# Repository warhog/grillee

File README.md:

# Grillee

## Legal
LotusGrill&reg; is a registered trademark of [LotusGrill GmbH](https://lotusgrill.de).

This project has in no way a connection to the LotusGrill GmbH. It is a private hobby project.

## License
GPLv3 licensed, see [LICENSE.md](license.md).

## Advice
Everything in this repo is provided as it is. I give no guarantee or take any responsibility for it. If you are not experienced with electronics you should at least have someone looking on your final build.

## Details
This project is a digital, bluetooth enabled control unit for LotusGrill&reg; styled grills. These kind of grills normally comes with a simple potentiometer for regulating the fan speed (correlating with the heat produces by the coal). After a few years of heavy usage of my LotusGrill&reg; the potentiometer was broken. Instead of replacing it I decided to create this control unit for improved handling.

Highlights:
* Bluetooth control (using an app)
* Manual (bluetoothless) control
* Fan rpm monitoring
* 2 built in grill thermometer probe connectors for various NTCs
* Battery voltage monitoring
* Alarming buzzer
* Webupdate

## App
The app is currently only available for Android on the Google Play Store. Due to the usage of the [Ionic Framework](https://ionicframework.com/) it can be also compiled for iOS.

Google Play Store: TODO: LINK

## Usage
### Fan control
The fan speed can either be controlled by the potentiometer (manual mode) or the app (using bluetooth). As soon as the app is connected the potentiometer is ignored.

### LED
The RGB LED shows the different states of operation. Blue light shows that the unit is in manual mode (potentiometer controls fan). Green light shows that bluetooth is connected. Both (blue and green light) show the selected fan speed using the brightness. The LED is blinking red in case of errors.

### Alarming

### Probes

### Update
Press the webupdate button and the reset button in parallel. Keep the webupdate button pressed while releasing the reset button and hold for 5 seconds. The board should start up in webupdate mode now. Search for a wifi network called `grillee-....`. The dots are the serial number of the ESP32 module. Connect to the wifi and browse the url: `http://192.168.4.1`. The web ui gives you the option to upload a new software.

## Control unit software
The control unit software is using Arduino on ESP32. The measurement data for the different sensors was taken from the WLANThermo Nano project ([source](https://github.com/WLANThermo-nano/WLANThermo_ESP32_Software/blob/master/src/temperature/TemperatureBase.cpp)).

The board has test pins for the serial connection to initially flash the software.

## Libraries used
MedianFilterLib2 v1.0.0

Mcp3208 v1.4.0

## Hardware
The hardware schematics, gerber files, ... can be found in the `hardware` folder. The components were chosen to be easy to obtain. 
The basic measurement circuit was taken from the WLANThermo Nano project ([schematics](https://github.com/WLANThermo-nano/WLANThermo_nano_Hardware/blob/master/nano%20v1%2B/circuit/Schaltplan%20WLANThermo%20Nano%20V1%2B.pdf)).

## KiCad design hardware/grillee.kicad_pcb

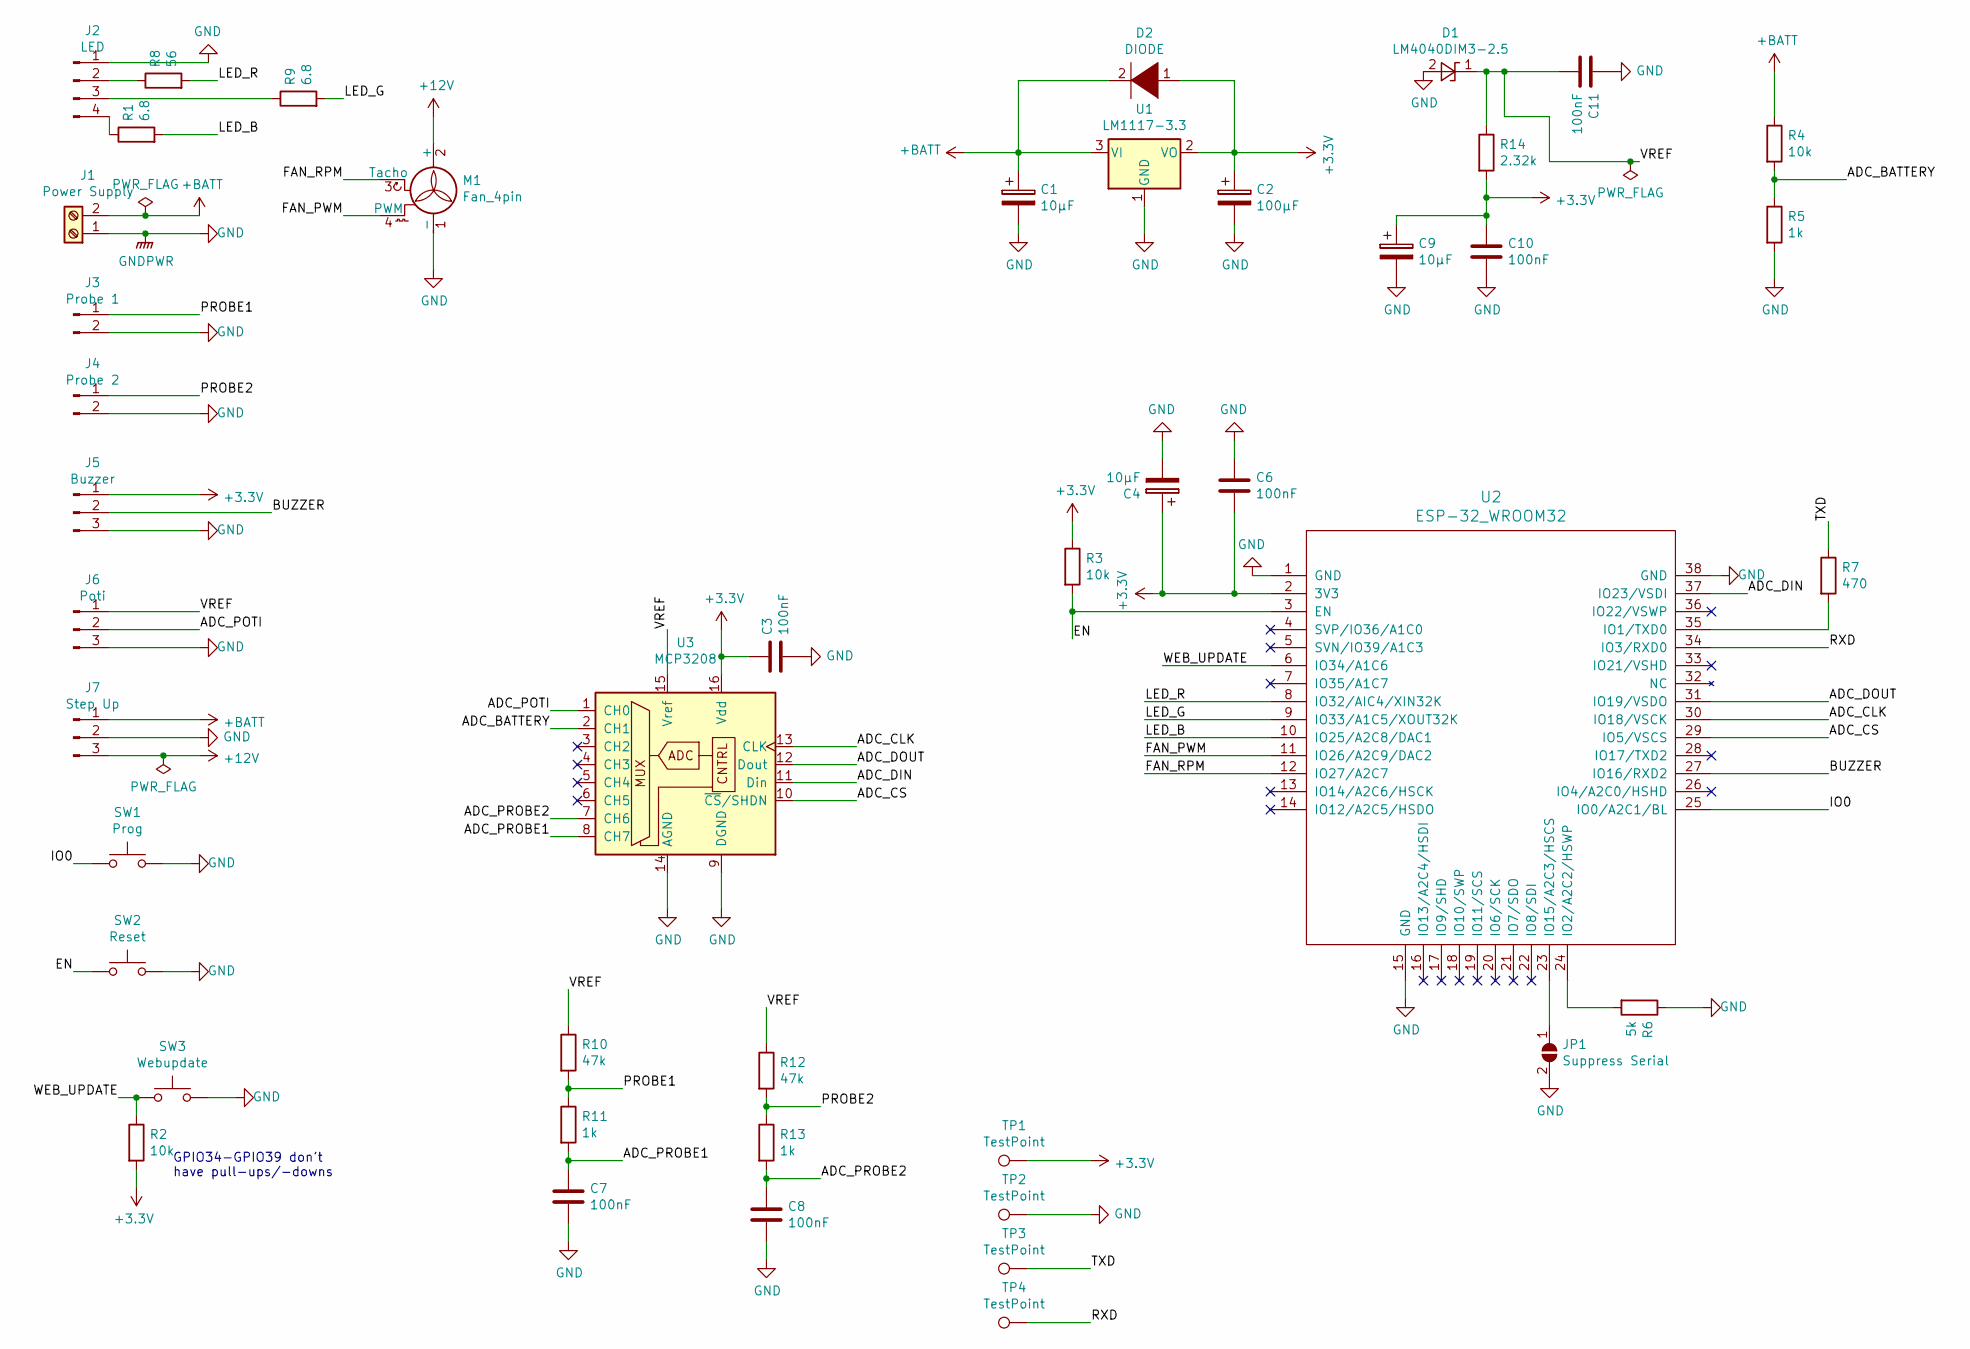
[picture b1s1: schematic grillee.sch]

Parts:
C1, C4: 10µF; CP_Elec_5x4.4
C2: 100µF; CP_Elec_6.3x5.4
C3, C6, C7, C8, C10, C11: 100nF; C_1206_3216Metric_Pad1.42x1.75mm_HandSolder
C9: 10µF; CP_Elec_6.3x5.4
D1: LM4040DIM3-2.5; SOT-23
D2: DIODE; D_SOD-323_HandSoldering
J1: Power Supply; TerminalBlock_RND_205-00287_1x02_P5.08mm_Horizontal
J2: LED; PinHeader_1x04_P2.54mm_Horizontal
J3: Probe 1; PinHeader_1x02_P2.54mm_Horizontal
J4: Probe 2; PinHeader_1x02_P2.54mm_Horizontal
J5: Buzzer; PinHeader_1x03_P2.54mm_Horizontal
J6: Poti; PinHeader_1x03_P2.54mm_Horizontal
J7: Step Up; PinHeader_1x03_P2.54mm_Horizontal
JP1: Suppress Serial; SolderJumper-2_P1.3mm_Open_RoundedPad1.0x1.5mm
M1: Fan_4pin; Molex_KK-254_AE-6410-04A_1x04_P2.54mm_Vertical
R1, R9: 6.8; R_1206_3216Metric_Pad1.42x1.75mm_HandSolder
R2, R3, R4: 10k; R_1206_3216Metric_Pad1.42x1.75mm_HandSolder
R5, R11, R13: 1k; R_1206_3216Metric_Pad1.42x1.75mm_HandSolder
R6: 5k; R_1206_3216Metric_Pad1.42x1.75mm_HandSolder
R7: 470; R_1206_3216Metric_Pad1.42x1.75mm_HandSolder
R8: 56; R_1206_3216Metric_Pad1.42x1.75mm_HandSolder
R10, R12: 47k; R_1206_3216Metric_Pad1.42x1.75mm_HandSolder
R14: 2.32k; R_Axial_DIN0204_L3.6mm_D1.6mm_P7.62mm_Horizontal
SW1: Prog; SW_SPST_KMR2
SW2: Reset; SW_SPST_KMR2
SW3: Webupdate; SW_SPST_KMR2
TP1, TP2, TP3, TP4: TestPoint; TestPoint_Pad_D1.5mm
U1: LM1117-3.3; SOT-223
U2: ESP-32_WROOM32; ESP32-WROOM
U3: MCP3208; SOIC-16_3.9x9.9mm_P1.27mm

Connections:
+3V3: C2.1, C3.1, C4.1, C6.2, C9.1, C10.1, D2.1 (K), J5.1, R2.2, R3.1, R14.2, TP1.1, U1.2 (VO), U2.2 (3V3), U3.16 (Vdd)
+12V: J7.3, M1.2 (+)
+BATT: C1.1, D2.2 (A), J1.2, J7.1, R4.1, U1.3 (VI)
/ADC_BATTERY: R4.2, R5.1, U3.2 (CH1)
/ADC_CLK: U2.30 (IO18/VSCK), U3.13 (CLK)
/ADC_CS: U2.29 (IO5/VSCS), U3.10 (~CS~/SHDN)
/ADC_DIN: U2.37 (IO23/VSDI), U3.11 (Din)
/ADC_DOUT: U2.31 (IO19/VSDO), U3.12 (Dout)
/ADC_POTI: J6.2, U3.1 (CH0)
/ADC_PROBE1: C7.1, R11.2, U3.8 (CH7)
/ADC_PROBE2: C8.1, R13.2, U3.7 (CH6)
/BUZZER: J5.2, U2.27 (IO16/RXD2)
/EN: R3.2, SW2.1, U2.3 (EN)
/FAN_PWM: M1.4 (PWM), U2.11 (IO26/A2C9/DAC2)
/FAN_RPM: M1.3 (Tacho), U2.12 (IO27/A2C7)
/IO0: SW1.1, U2.25 (IO0/A2C1/BL)
/LED_B: R1.2, U2.10 (IO25/A2C8/DAC1)
/LED_G: R9.2, U2.9 (IO33/A1C5/XOUT32K)
/LED_R: R8.2, U2.8 (IO32/AIC4/XIN32K)
/PROBE1: J3.1, R10.2, R11.1
/PROBE2: J4.1, R12.2, R13.1
/RXD: TP4.1, U2.34 (IO3/RXD0)
/TXD: R7.1, TP3.1
/VREF: C11.2, D1.1 (K), J6.1, R10.1, R12.1, R14.1, U3.15 (Vref)
/WEB_UPDATE: R2.1, SW3.1, U2.6 (IO34/A1C6)
GND: C1.2, C2.2, C3.2, C4.2, C6.1, C7.2, C8.2, C9.2, C10.2, C11.1, D1.2 (A), J1.1, J2.1, J3.2, J4.2, J5.3, J6.3, J7.2, JP1.2 (B), M1.1 (-), R5.2, R6.1, SW1.2, SW2.2, SW3.2, TP2.1, U1.1 (GND), U2.1 (GND), U2.15 (GND), U2.38 (GND), U3.9 (DGND), U3.14 (AGND)
unnamed: J2.2, R8.1
unnamed: J2.3, R9.1
unnamed: J2.4, R1.1
unnamed: JP1.1 (A), U2.23 (IO15/A2C3/HSCS)
unnamed: R6.2, U2.24 (IO2/A2C2/HSWP)
unnamed: R7.2, U2.35 (IO1/TXD0)

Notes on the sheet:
GPIO34-GPIO39 don't have pull-ups/-downs

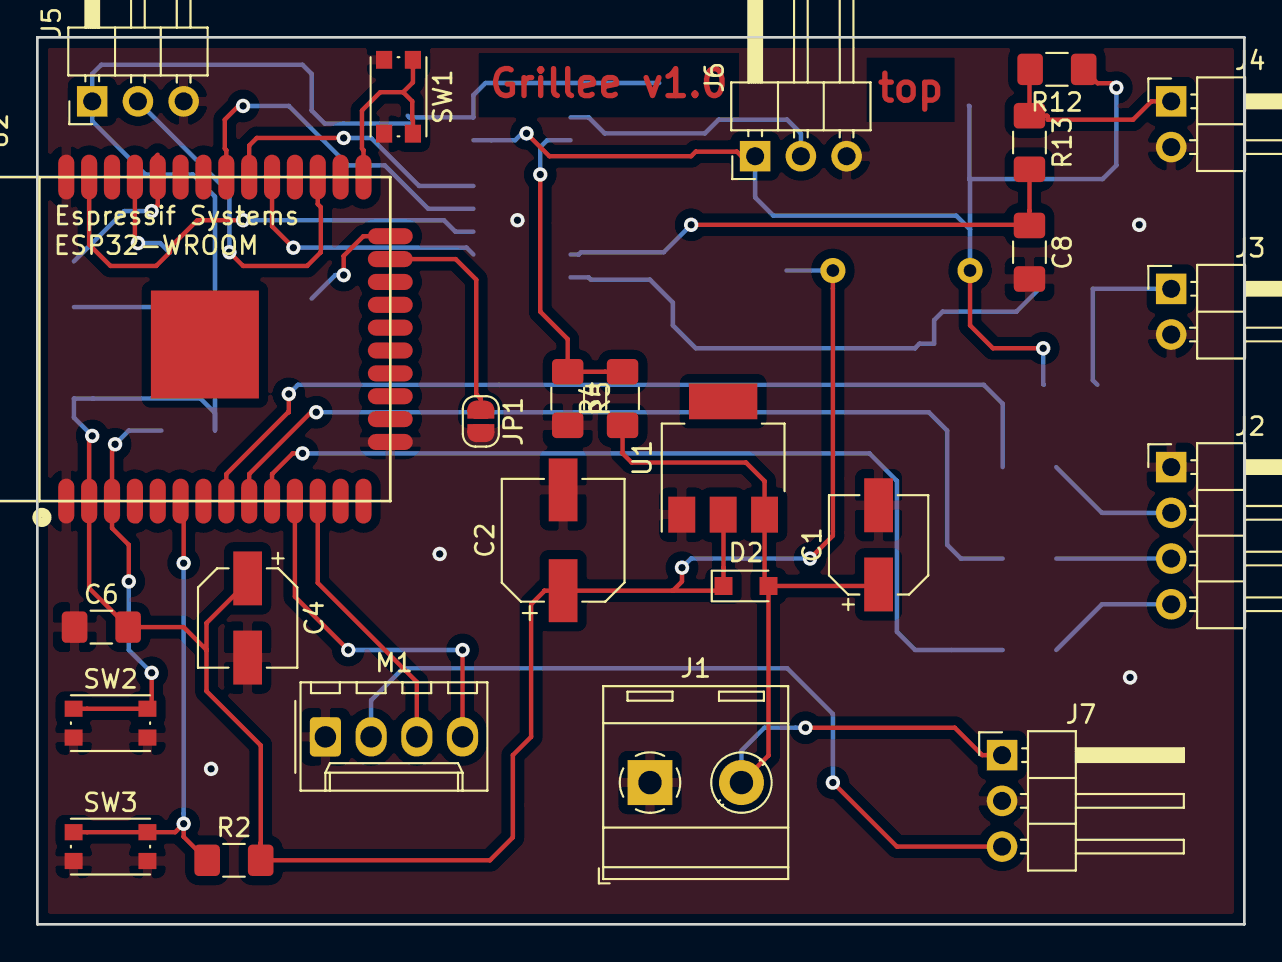
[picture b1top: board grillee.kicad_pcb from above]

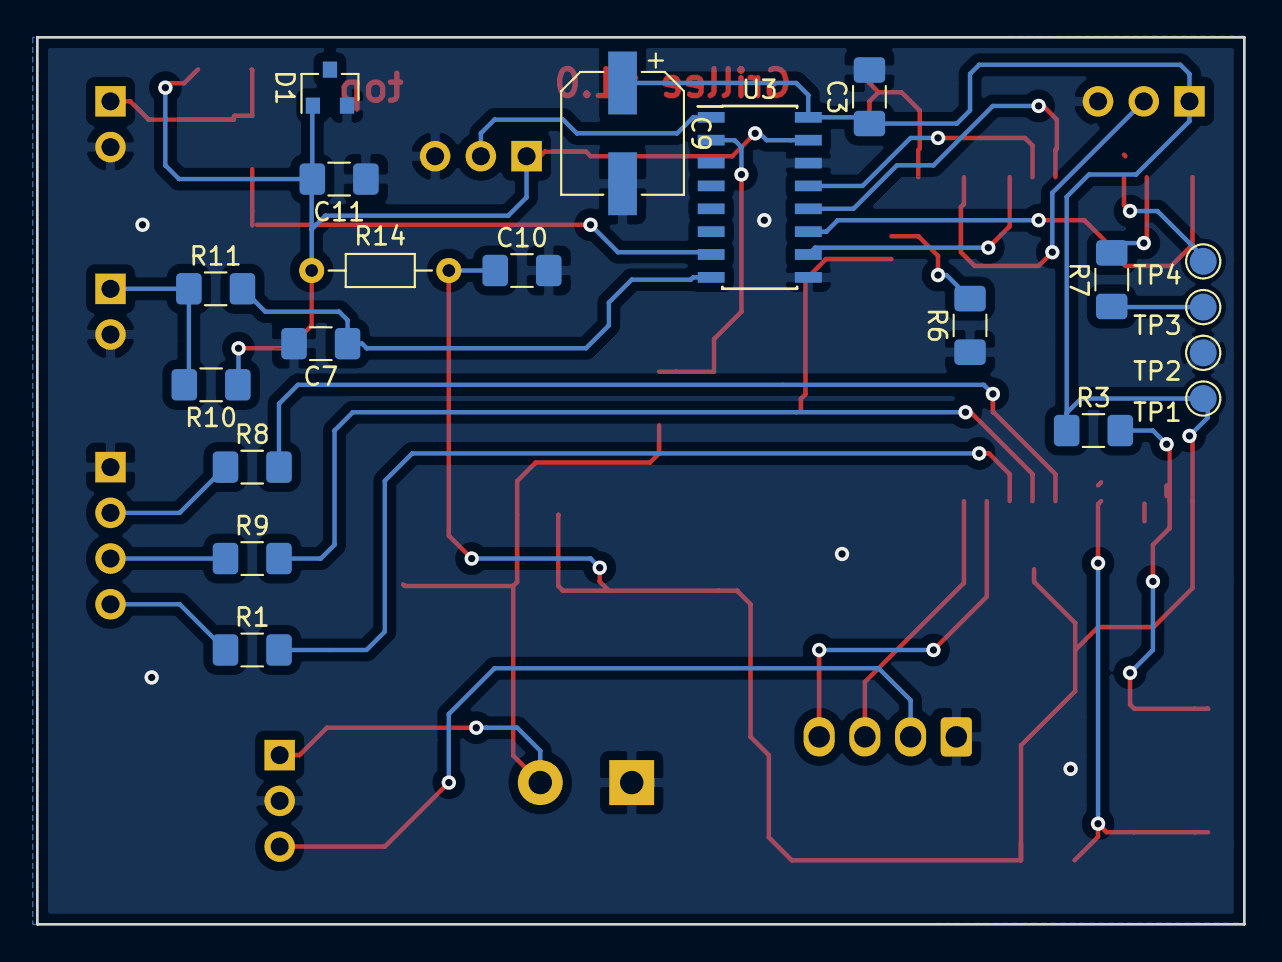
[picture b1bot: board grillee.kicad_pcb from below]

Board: 2 copper layers, 67.1 x 49.3 mm, 45 parts (20 on the bottom side), 32 nets.

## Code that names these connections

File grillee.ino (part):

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const gpio_num_t PIN_FAN = GPIO_NUM_26;
const gpio_num_t PIN_RPM = GPIO_NUM_27;
const gpio_num_t PIN_ALARM_BUZZER = GPIO_NUM_16;
const gpio_num_t PIN_ADC_CS = GPIO_NUM_5;
const gpio_num_t PIN_LED_R = GPIO_NUM_32;
const gpio_num_t PIN_LED_G = GPIO_NUM_33;
const gpio_num_t PIN_LED_B = GPIO_NUM_25;
const gpio_num_t PIN_WEB_UPDATE = GPIO_NUM_34;

// adc chip io channel definition
const MCP3208::Channel ADC_CHANNEL_BATTERY = MCP3208::Channel::SINGLE_1;
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EdgeDetector<int16_t> probe2Changed(0, 1);

ble::BleServer bleServer;
util::Led ledR(PIN_LED_R, util::LEDC_CHANNEL_LED_R, true);
util::Led ledG(PIN_LED_G, util::LEDC_CHANNEL_LED_G, true);
util::Led ledB(PIN_LED_B, util::LEDC_CHANNEL_LED_B, true);

util::Adc_MCP3208 adcMcp3208;
util::Storage storage;
util::Buzzer buzzer(PIN_ALARM_BUZZER);
util::Battery battery(&adcMcp3208, ADC_CHANNEL_BATTERY);

measurement::Probe probe1(&adcMcp3208, ADC_CHANNEL_PROBE0, SensorType::UNKNOWN);
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    
    // in debug mode always enable webupdate feature
#ifndef DEBUG
	pinMode(PIN_WEB_UPDATE, INPUT_PULLUP);
	if (digitalRead(PIN_WEB_UPDATE) == LOW) {
#endif
#ifdef DEBUG
		Serial.println(F("force wifi ap mode"));
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
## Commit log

2020-05-05 inital dev version
2020-05-05 lot of changes
2020-05-05 added license
2020-05-06 working probes
2020-05-11 before menu
2020-05-11 added sidemenu
2020-05-13 lot of changes, fixed data transmission between device and app
2020-05-13 lot of fixes and improvements
2020-05-14 improve ble read and register
2020-05-15 added mcp3208 adc, many improvements
2020-05-15 added first step of alarming, improvemetns and fixes
2020-05-16 first version of alarming working
2020-05-16 removed unused model
2020-05-16 improve buzzer sound, some bugfixes
2020-05-22 lots of fixes, added translations, improved resourcs
2020-05-22 add connection timeout
2020-06-05 new pin layout, added datasheets
2020-07-25 lot of updates
2020-08-02 fixed ledc pwm setup
2020-08-02 change buzzer state order
2020-08-03 improved alarm handling
2020-08-07 lot of improvements
2020-08-08 fixed alarm foter position, moved alarm to separate component
2020-08-08 added ble not available message to home screen
2020-08-08 add alarm state output, disable debug, add alarm ack bit
2020-08-08 remove commented code
2020-08-08 remove temperature printing to console
2020-08-08 remove unused code
2020-08-08 fix background mode
2020-08-14 fixed adc channel order, reordered ledc channels
2020-08-15 added back button callback to suppress background mode on exit
2020-08-15 correct battery voltage divider comment
2020-08-22 updated app versions
2020-08-22 fix adc, add led gamma correction
2020-08-22 add travis build
2020-08-22 added hardware stuff
2020-08-22 fix travis build
2020-08-29 add storage of last selected probe temperature, add help texts
2020-08-29 added gpl headers
2020-08-29 added license headers, removed old adc, changed to medianfilterlib2, travis build improvements, splitted huge libs, improve led handling, some small fixes
2020-08-29 added readme for sensor data
2020-08-29 added keystore to gitignore
2020-08-29 revoke test release keystore
2020-08-30 renamed
2020-08-30 revert to initial (working) npm versions
2020-09-19 update deps
2020-09-19 updated to angular 9
2020-09-19 updated to angular 10, added app resource documentation
2020-09-19 updated documentation
2020-09-19 some changes
2020-09-19 document libraries used
2020-09-19 add arduinojson to travis build
2020-09-19 remove flash_node.sh from travis build
2020-09-19 fix travis build?
2020-09-19 try to fix travis buidl
2020-09-19 try to fix travis build
2021-03-11 Bump elliptic from 6.5.3 to 6.5.4 in /grillee-app
    Bumps [elliptic](https://github.com/indutny/elliptic) from 6.5.3 to 6.5.4.
    - [Release notes](https://github.com/indutny/elliptic/releases)
    - [Commits](https://github.com/indutny/elliptic/compare/v6.5.3...v6.5.4)
2021-03-28 updated versions to work with android 10
2021-04-01 Bump y18n from 4.0.0 to 4.0.1 in /grillee-app
    Bumps [y18n](https://github.com/yargs/y18n) from 4.0.0 to 4.0.1.
    - [Release notes](https://github.com/yargs/y18n/releases)
    - [Changelog](https://github.com/yargs/y18n/blob/master/CHANGELOG.md)
    - [Commits](https://github.com/yargs/y18n/commits)
2021-04-30 Bump ssri from 6.0.1 to 6.0.2 in /grillee-app
    Bumps [ssri](https://github.com/npm/ssri) from 6.0.1 to 6.0.2.
    - [Release notes](https://github.com/npm/ssri/releases)
    - [Changelog](https://github.com/npm/ssri/blob/v6.0.2/CHANGELOG.md)
    - [Commits](https://github.com/npm/ssri/compare/v6.0.1...v6.0.2)
2021-05-10 Bump url-parse from 1.4.7 to 1.5.1 in /grillee-app
    Bumps [url-parse](https://github.com/unshiftio/url-parse) from 1.4.7 to 1.5.1.
    - [Release notes](https://github.com/unshiftio/url-parse/releases)
    - [Commits](https://github.com/unshiftio/url-parse/compare/1.4.7...1.5.1)
2021-05-11 Bump lodash from 4.17.20 to 4.17.21 in /grillee-app
    Bumps [lodash](https://github.com/lodash/lodash) from 4.17.20 to 4.17.21.
    - [Release notes](https://github.com/lodash/lodash/releases)
    - [Commits](https://github.com/lodash/lodash/compare/4.17.20...4.17.21)
2021-05-11 Bump hosted-git-info from 2.8.8 to 2.8.9 in /grillee-app
    Bumps [hosted-git-info](https://github.com/npm/hosted-git-info) from 2.8.8 to 2.8.9.
    - [Release notes](https://github.com/npm/hosted-git-info/releases)
    - [Changelog](https://github.com/npm/hosted-git-info/blob/v2.8.9/CHANGELOG.md)
    - [Commits](https://github.com/npm/hosted-git-info/compare/v2.8.8...v2.8.9)

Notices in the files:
grillee.ino:
Copyright (C) 2020 warhog <warhog@gmx.de>
This program is free software: you can redistribute it and/or modify
it under the terms of the GNU General Public License as published by
the Free Software Foundation, either version 3 of the License, or
(at your option) any later version.
